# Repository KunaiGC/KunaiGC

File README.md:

# KunaiGC
It is a OpenSource IPL modchip for the Nintendo Gamecube which provides a rich featureset. 

## Features
* QSB - Quick Solder Board for easy installation process
* Flash storage - boot directly into internal Swiss or GBI (Game Boy Interface)
* configurable boot-behavior
* Button mapped .dol file loading 
* Boot discs from all regions via build-in swiss
* KunaiUpdater - Update/Install Firmware, internal Swiss and GBI (Game Boy Interface) via SD-Card
* KunaiRecovery
* Cubeboot support

## Guides and Wiki

* just take a look at MachoNachos video:
[The Gamecube Just Got A NEW Modchip | The kunaiGC](https://www.youtube.com/watch?v=YmsjPn3J_iU)
* visit our [**Wiki-Page**](https://github.com/KunaiGC/KunaiGC/wiki) for detailed informations

## Installation

* The QSB is pretty straight forward and you only need to solder a few given spots. Make sure to check [**the solder guide**](https://github.com/KunaiGC/KunaiGC/wiki/Installation)

## Update the KunaiGC
* To update the KunaiGC firmware, the internal swiss version or install gbi (Game Boy Interface) please follow the [update instructions](https://github.com/KunaiGC/KunaiGC/wiki/Update-the-KunaiGC)

## You want to support our development?

head over to your favorite shop and order your own KunaiGC
* [Swiss] consoles4you: https://consoles4you.ch/en/kunaigc-mod-chip
* [US] stoneagegamer: https://stoneagegamer.com/kunaigc.html
* [France] mod in france: https://shop.modinfrance.fr/en/gamecube/60-kunaigc-for-gamecube.html
* [UK] retro upgrades: https://www.retroupgrades.co.uk/product/kunaigc-modchip/

## Credits
* #gc-forever crew: [Extrems](https://github.com/Extrems), [emu_kidid](https://github.com/emukidid) for doing the best job on swiss and homebrew, [novenary](https://github.com/9ary) especially for gaving us the permission to make his [gc-ipl](https://github.com/redolution/gc-ipl) great again 
* [tmbinc](https://github.com/tmbinc) - making ipl modchips possible
* happy_bunny and [webhdx](https://github.com/webhdx) for their research on the [shuriken attack](https://www.retro-system.com/shuriken_attack.htm) and [PicoBoot](https://github.com/webhdx/PicoBoot)
* KunaiGC beta testers from [CiBo](https://circuit-board.de/forum/), [psxtools.de](psxtools.de) and [EnterpriseFreak](https://github.com/EnterpriseFreak-v2)
* The handsome guys :p [Voultar](https://voultar.com/) and [MachoNacho](https://www.youtube.com/c/MachoNachoProductions)
* everyone who supports us 

## Licence 
 * The Hardware was developed under CC BY-NC-SA (Creative Commons Attribution-NonCommercial-ShareAlike 4.0 International)
 * The Software was developed under GNU GPL 2 (GNU GENERAL PUBLIC LICENSE 2)

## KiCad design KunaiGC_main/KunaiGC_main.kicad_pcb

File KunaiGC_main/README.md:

# KunaiGC main PCB
The actual Modchip.

for its BOM please see [the Wiki](https://github.com/KunaiGC/KunaiGC/wiki/Build-the-KunaiGC)

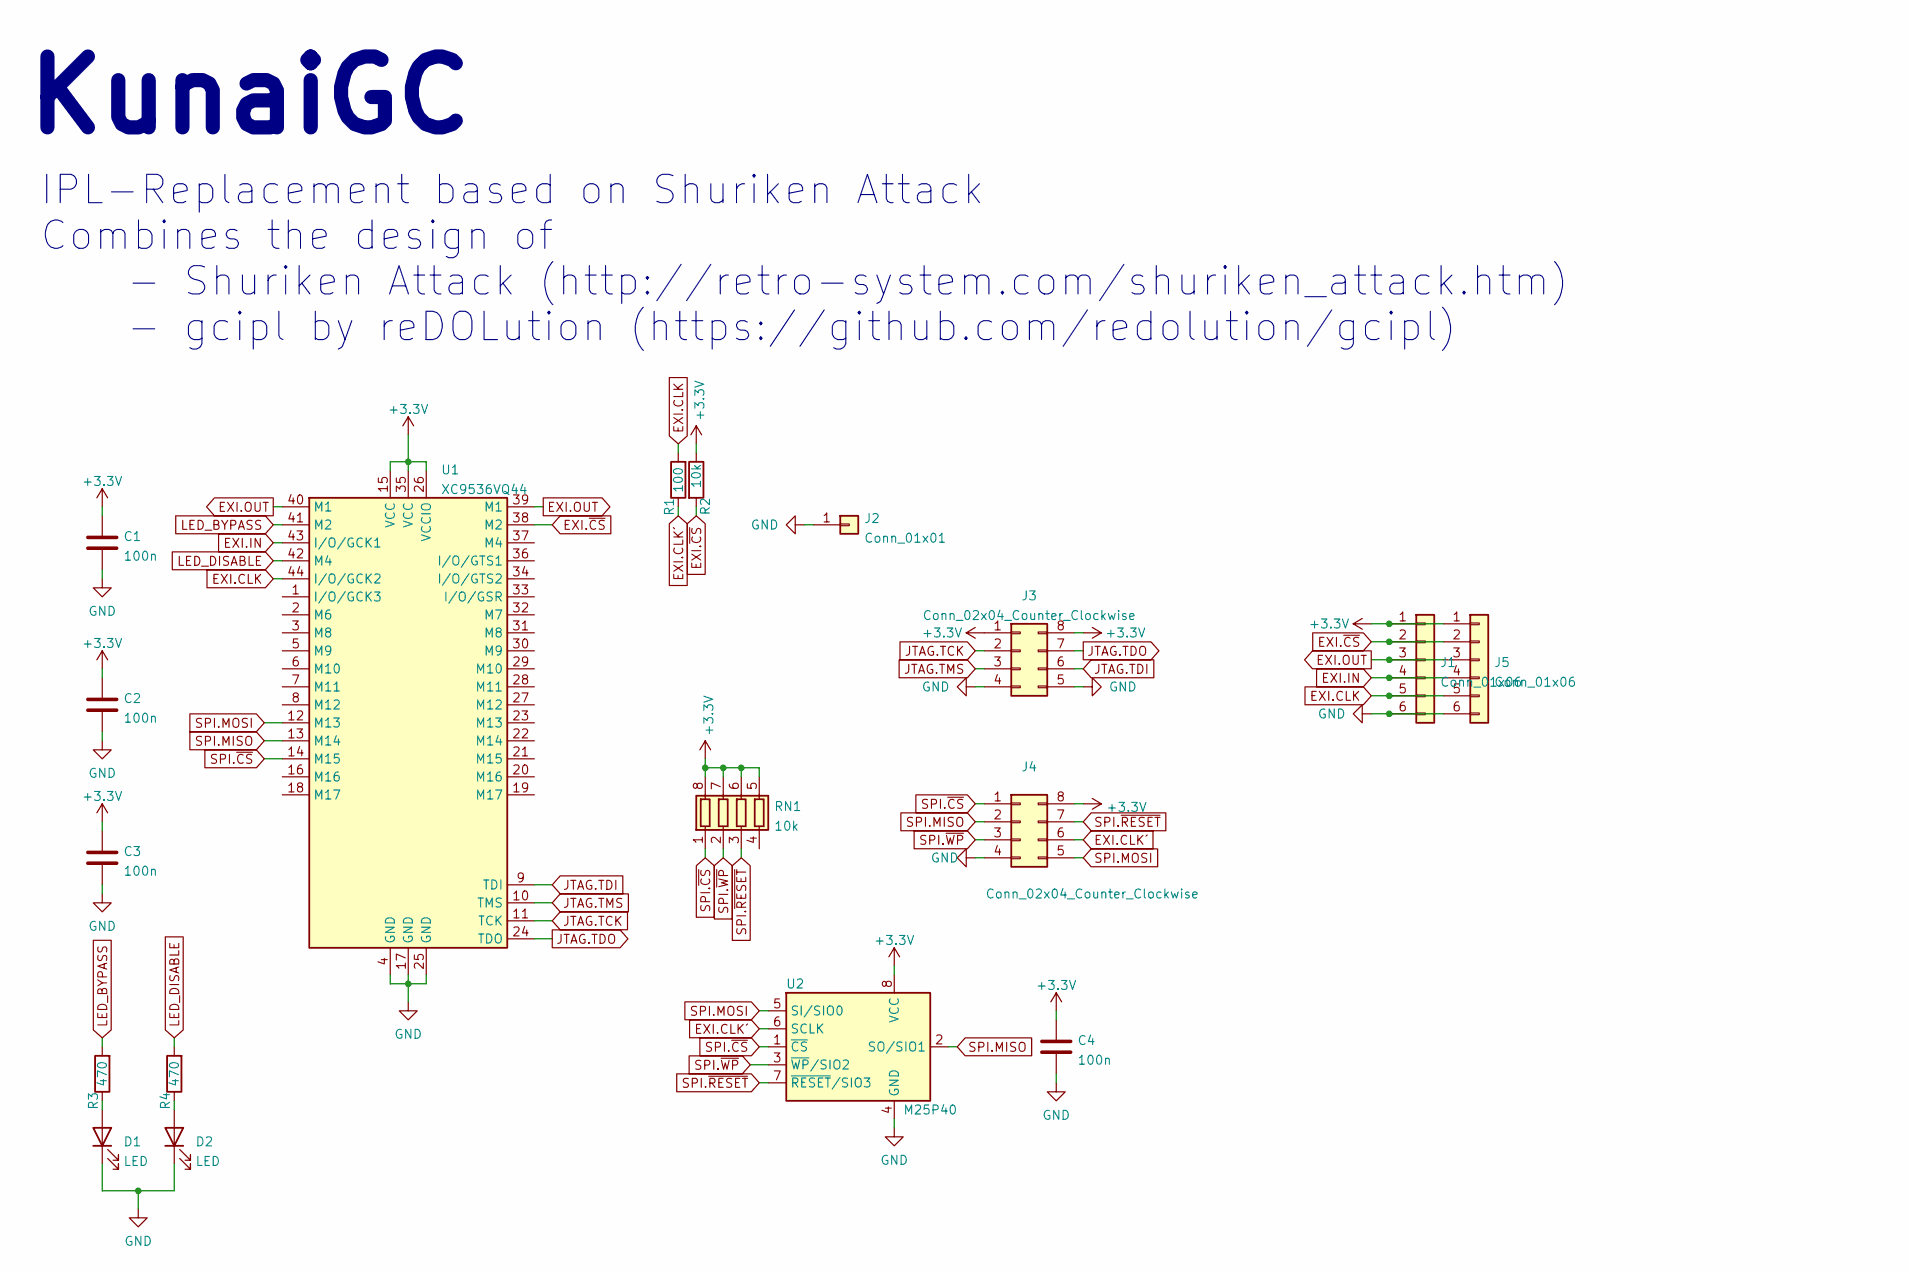
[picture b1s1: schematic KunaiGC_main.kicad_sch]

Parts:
C1, C2, C3, C4: 100n; C_0805_2012Metric
D1, D2: LED; LED_0805_2012Metric
J1, J5: Conn_01x06; PinHeader_1x06_P2.54mm_Vertical
J2: Conn_01x01; TestPoint_Pad_1.5x1.5mm
J3, J4: Conn_02x04_Counter_Clockwise; SOIC_clipProgSmall
R1: 100; R_0805_2012Metric
R2: 10k; R_0805_2012Metric
R3, R4: 470; R_0805_2012Metric
RN1: 10k; R_Array_Concave_4x0603
U1: XC9536VQ44; TQFP-44_10x10mm_P0.8mm
U2: M25P40; SOP-8-Wide

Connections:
+3V3: C1.1, C2.1, C3.1, C4.1, J1.1, J3.1, J3.8, J4.8, J5.1, R2.1, RN1.5 (R4.2), RN1.6 (R3.2), RN1.7 (R2.2), RN1.8 (R1.2), U1.15 (VCC), U1.26 (VCCIO), U1.35 (VCC), U2.8 (VCC)
EXI.CLK: J1.5, J5.5, R1.2, U1.44 (I/O/GCK2)
EXI.CLK´: J4.6, R1.1, U2.6 (SCLK)
EXI.IN: J1.4, J5.4, U1.43 (I/O/GCK1)
EXI.OUT: J1.3, J5.3, U1.39 (M1), U1.40 (M1)
EXI.~CS: J1.2, J5.2, R2.2, U1.38 (M2)
GND: C1.2, C2.2, C3.2, C4.2, D1.1 (K), D2.1 (K), J1.6, J2.1, J3.4, J3.5, J4.4, J5.6, U1.4 (GND), U1.17 (GND), U1.25 (GND), U2.4 (GND)
JTAG.TCK: J3.2, U1.11 (TCK)
JTAG.TDI: J3.6, U1.9 (TDI)
JTAG.TDO: J3.7, U1.24 (TDO)
JTAG.TMS: J3.3, U1.10 (TMS)
LED_BYPASS: R3.2, U1.41 (M2)
LED_DISABLE: R4.2, U1.42 (M4)
unnamed: D1.2 (A), R3.1
unnamed: D2.2 (A), R4.1
SPI.MISO: J4.2, U1.13 (M14), U2.2 (SO/SIO1)
SPI.MOSI: J4.5, U1.12 (M13), U2.5 (SI/SIO0)
SPI.~CS: J4.1, RN1.1 (R1.1), U1.14 (M15), U2.1 (~CS)
SPI.~RESET: J4.7, RN1.3 (R3.1), U2.7 (~RESET/SIO3)
SPI.~WP: J4.3, RN1.2 (R2.1), U2.3 (~WP/SIO2)

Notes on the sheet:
IPL-Replacement based on Shuriken Attack Combines the design of - Shuriken Attack (http://retro-system.com/shuriken_attack.htm) - gcipl by reDOLution (https://github.com/redolution/gcipl)
KunaiGC

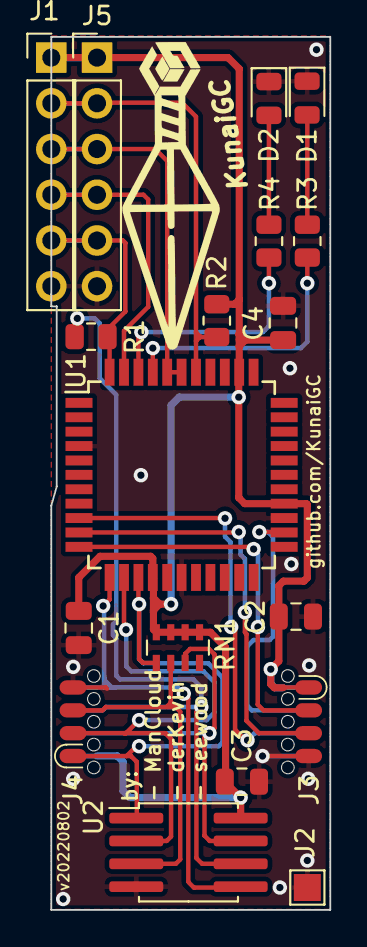
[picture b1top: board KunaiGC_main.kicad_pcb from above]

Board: 2 copper layers, 15.5 x 48.5 mm, 18 parts (0 on the bottom side), 20 nets.

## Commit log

2022-06-28 wip image
2022-08-02 added PCB-Files
2022-08-02 updated sources + makefiles
2022-08-16 added QSB for DOL-101
2022-10-30 Implemented LFS into KunaiRecovery
2023-04-20 relocated images and add detailed installaion
2023-04-20 cleaned up files
2023-04-20 clean up and add detailed installation images
2023-04-20 updated kunai image
2023-04-20 updated logo image
2023-04-20 more informations added
2023-04-20 wrong filename
2023-04-20 added proper images
2023-04-27 added proper links
2023-05-12 new image
2023-05-12 added new link
2023-05-12 added links
2023-05-15 updated to latest files
2023-05-15 Merge (#3)
    * initial commit
    * added PCB-Files
    * updated sources + makefiles
    * added QSB for DOL-101
    * Implemented LFS into KunaiRecovery
    * updated to latest files
2023-05-16 Update README.md
    * Added Licences
2023-06-02 added MiF
2023-06-08 Update README.md
    Added more shops
2023-10-04 Fix: Increase offset during multi block write
2023-10-04 Add Debug Capabilities for SPI
2023-10-04 Fix: Increase Offset during Multi Block Write (#14)
    * Fix: Increase offset during multi block write
    * Add Debug Capabilities for SPI
    ---------
2023-11-23 KunaiUpdater added
2023-11-23 added for issue #5
    added for issue #5 https://github.com/KunaiGC/KunaiGC/issues/5
2024-03-21 updating wiki
2024-03-21 update wiki
2024-03-22 Updateing wiki
